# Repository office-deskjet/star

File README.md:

# About
How to use Inkscape and KiCad to make cool looking boards.

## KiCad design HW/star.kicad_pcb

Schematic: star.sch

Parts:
BT1: Battery_Cell; CR2030_Retainer
D1, D2, D3, D4, D5: LED; LED_D3.0mm
R1, R2, R3, R4, R5: 100R; R_Axial_DIN0207_L6.3mm_D2.5mm_P7.62mm_Horizontal
U1: ATtiny85V-10SU; SOIJ-8_5.3x5.3mm_P1.27mm

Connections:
/LED1: R1.2, U1.5 (AREF/PB0)
/LED2: R2.2, U1.6 (PB1)
/LED3: R3.2, U1.7 (PB2)
/LED4: R4.2, U1.2 (XTAL1/PB3)
/LED5: R5.2, U1.3 (XTAL2/PB4)
/NC: U1.1 (~RESET~/PB5)
/VCC: BT1.1, U1.8 (VCC)
GND: BT1.2, D1.1, D2.1, D3.1, D4.1, D5.1, U1.4 (GND)
unnamed: D1.2, R1.1
unnamed: D2.2, R2.1
unnamed: D3.2, R3.1
unnamed: D4.2, R4.1
unnamed: D5.2, R5.1

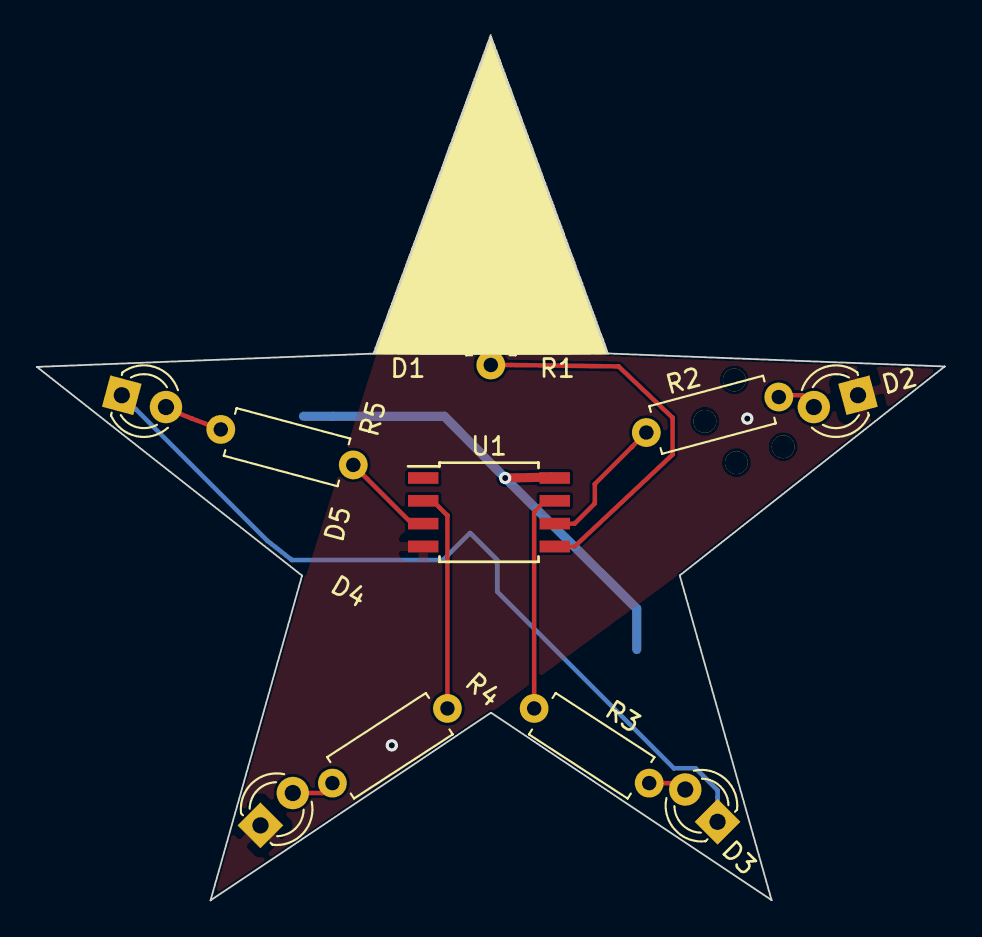
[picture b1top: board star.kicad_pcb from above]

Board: 2 copper layers, 50.4 x 48.0 mm, 12 parts (1 on the bottom side), 12 nets.

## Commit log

2018-09-24 added art and started schematic
2018-09-24 added gitignor and ref desg
2018-09-24 moved directory, added net
2018-09-24 done with layout
2018-09-24 idk stuff changed
